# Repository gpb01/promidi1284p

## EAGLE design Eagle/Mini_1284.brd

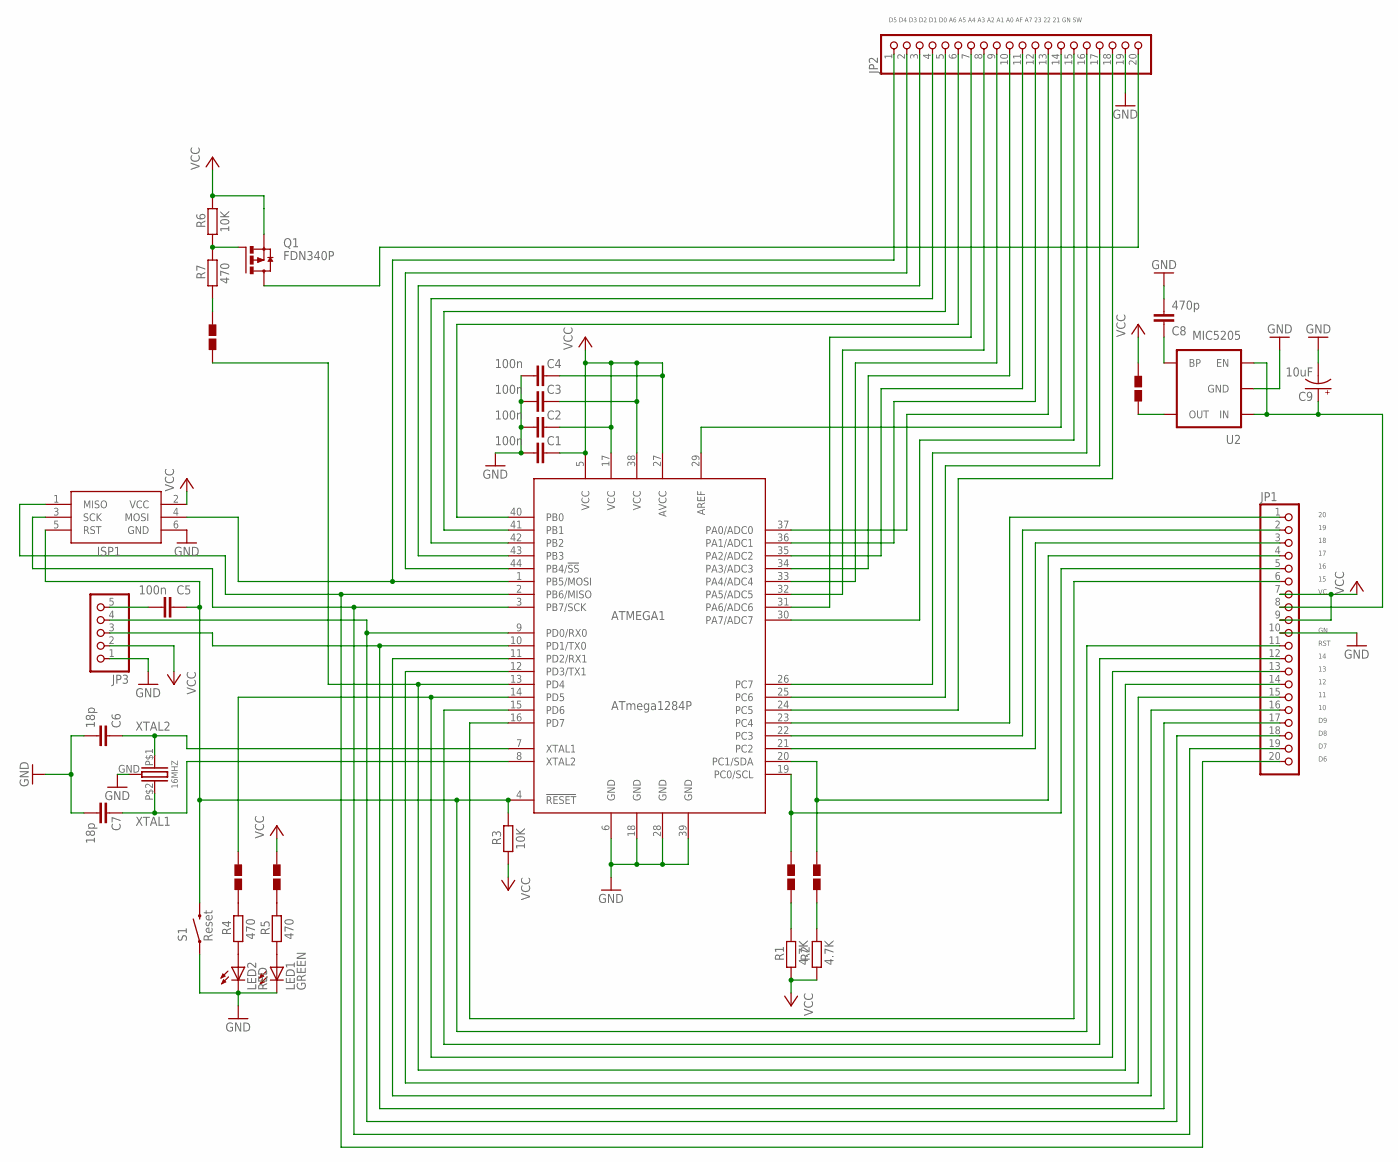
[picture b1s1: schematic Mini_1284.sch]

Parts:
16MHZ: CX2520
ATMEGA1: ATmega1284P; 44TQFP
C1, C2, C3, C4, C5: 100n; C0603-ROUND
C6, C7: 18p; C0603-ROUND
C8: 470p; C0603-ROUND
C9: 10uF; EIA3216
ISP1: AVRISP-6; AVRISP
JP1, JP2: PINHD-1X20; 1X20
JP3: PINHD-1X5; 1X05
LED1: GREEN; CHIP-LED0805
LED2: RED; CHIP-LED0805
Q1: FDN340P; SUPER-SOT3
R1, R2: 4.7K; R0603-ROUND
R3, R6: 10K; R0603-ROUND
R4, R5, R7: 470; R0603-ROUND
S1: Reset; TACTILE-SWITCH-SMD-ALT01
U2: MIC5205; SOT23-5
U$4, U$5, U$8, U$9, U$12, U$13: SOL-PAD-OPEN

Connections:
GND: 16MHZ.GND, ATMEGA1.6 (GND), ATMEGA1.18 (GND), ATMEGA1.28 (GND), ATMEGA1.39 (GND), C1.2, C2.2, C3.2, C4.2, C6.2, C7.2, C8.2, C9.C (-), ISP1.6 (GND), JP1.10, JP2.19, JP3.1, LED1.C, LED2.C, S1.1, S1.2 (1), U2.2 (GND)
unnamed: ATMEGA1.4 (!RESET), C5.1, ISP1.5 (RST), JP1.11, R3.2, S1.3 (2), S1.4 (2)
unnamed: C5.2, JP3.5
unnamed: LED2.A, R4.1
unnamed: ATMEGA1.10 (PD1/TX0), JP1.17, JP3.3
unnamed: ATMEGA1.9 (PD0/RX0), JP1.18, JP3.4
unnamed: R1.2, U$4.P$1 (1)
unnamed: ATMEGA1.20 (PC1/SDA), JP1.4, U$12.P$1 (1)
unnamed: LED1.A, R5.1
unnamed: R5.2, U$8.P$1 (1)
unnamed: ATMEGA1.3 (PB7/SCK), ISP1.3 (SCK), JP1.19
unnamed: ATMEGA1.2 (PB6/MISO), ISP1.1 (MISO), JP1.20
unnamed: ATMEGA1.1 (PB5/MOSI), ISP1.4 (MOSI), JP2.1
unnamed: R4.2, U$9.P$1 (1)
unnamed: ATMEGA1.14 (PD5), JP1.13, U$9.P$2 (2)
unnamed: R2.2, U$12.P$2 (2)
unnamed: ATMEGA1.23 (PC4), JP1.1
unnamed: ATMEGA1.19 (PC0/SCL), JP1.5, U$4.P$2 (2)
unnamed: ATMEGA1.16 (PD7), JP1.6
unnamed: ATMEGA1.15 (PD6), JP1.12
unnamed: ATMEGA1.40 (PB0), JP2.6
unnamed: ATMEGA1.21 (PC2), JP1.3
unnamed: ATMEGA1.22 (PC3), JP1.2
unnamed: ATMEGA1.13 (PD4), JP1.14, U$5.P$1 (1)
unnamed: ATMEGA1.12 (PD3/TX1), JP1.15
unnamed: ATMEGA1.11 (PD2/RX1), JP1.16
unnamed: ATMEGA1.41 (PB1), JP2.5
unnamed: ATMEGA1.42 (PB2), JP2.4
unnamed: ATMEGA1.43 (PB3), JP2.3
unnamed: ATMEGA1.44 (PB4/!SS), JP2.2
unnamed: ATMEGA1.36 (PA1/ADC1), JP2.12
unnamed: ATMEGA1.31 (PA6/ADC6), JP2.7
unnamed: ATMEGA1.32 (PA5/ADC5), JP2.8
unnamed: ATMEGA1.33 (PA4/ADC4), JP2.9
unnamed: ATMEGA1.34 (PA3/ADC3), JP2.10
unnamed: ATMEGA1.35 (PA2/ADC2), JP2.11
unnamed: ATMEGA1.37 (PA0/ADC0), JP2.13
unnamed: ATMEGA1.29 (AREF), JP2.14
unnamed: ATMEGA1.30 (PA7/ADC7), JP2.15
unnamed: ATMEGA1.26 (PC7), JP2.16
unnamed: ATMEGA1.25 (PC6), JP2.17
unnamed: ATMEGA1.24 (PC5), JP2.18
unnamed: U2.5 (OUT), U$13.P$2 (2)
unnamed: C8.1, U2.4 (BP)
unnamed: Q1.1 (G), R6.1, R7.2
unnamed: JP2.20, Q1.3 (D)
unnamed: R7.1, U$5.P$2 (2)
RAW: C9.A (+), JP1.8, U2.1 (IN), U2.3 (EN)
VCC: ATMEGA1.5 (VCC), ATMEGA1.17 (VCC), ATMEGA1.27 (AVCC), ATMEGA1.38 (VCC), C1.1, C2.1, C3.1, C4.1, ISP1.2 (VCC), JP1.7, JP1.9, JP3.2, Q1.2 (S), R1.1, R2.1, R3.1, R6.2, U$8.P$2 (2), U$13.P$1 (1)
XTAL1: 16MHZ.P$2 (XTAL2), ATMEGA1.8 (XTAL2), C7.1
XTAL2: 16MHZ.P$1 (XTAL1), ATMEGA1.7 (XTAL1), C6.1

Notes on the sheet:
D5 D4 D3 D2 D1 D0 A6 A5 A4 A3 A2 A1 A0 AF A7 23 22 21 GN SW
20 19 18 17 16 15 VC GN RST 14 13 12 11 10 D9 D8 D7 D6

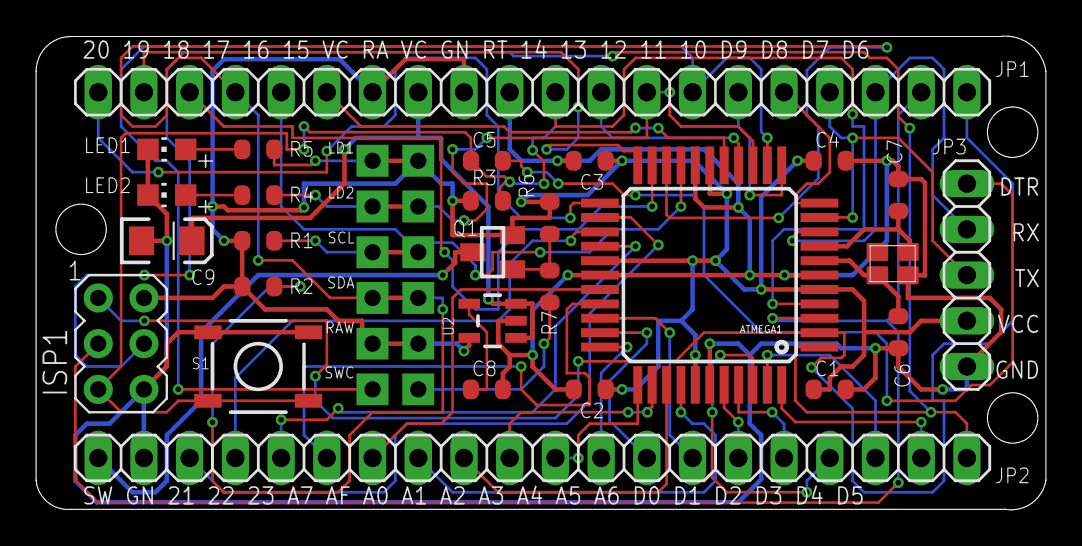
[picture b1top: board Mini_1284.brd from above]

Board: 2 copper layers, 56.1 x 26.3 mm, 33 parts (0 on the bottom side), 51 nets.

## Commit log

2024-04-17 ProMidi1284P production files
